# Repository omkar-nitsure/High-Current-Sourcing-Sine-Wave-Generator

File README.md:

# High Current Sourcing Sine Wave Generator

Group Members -

1. Omkar Nitsure - 210070057
2. Ojas Karanjkar - 210070040
3. Kushal Gajbe - 210070048
4. Vaibhav Garg - 21d070085 <br>
Github Link - [All files and code Contents](https://github.com/omkar-nitsure/High_Current_Sourcing_Sine_Wave_Generator)

## Introduction

Magnetic Materials are used in many application and in many different equipment for their special properties. But before using them, we need to have in-depth knowledge of their characteristics. This requires performing BH characterization. In BH characterization, we need to apply a sinusoidal voltage of varying amplitude and frequency across the magnetic material and check for the current it draws. Then the current and voltage information can be used to compute the value of B and H. The area enclosed by this curve is an indication of the amount of power dissipation in the material. This and other information is vital for choosing the right material for a specific application.

So, now we understand why BH characterization is important. We need a source which is able to generate a sinusoidal voltage with varying amplitude and frequency and source the current drawn by the magnetic material. The aim of our project is to design such a source.

This problem can be tackled either using a digital + analog or only analog approach. We tried both approaches. We designed an analog only circuit comprising of Class-AB amplifier and for the digital + analog we have used a Class-D amplifier based circuit. Let's discuss both the approaches in the following sections -

## Target Specifications

We were required to build a source satisfying the above constraints -

- Output Frequency = 2-3 kHz
- Output Sine amplitude = upto 30 Vpp
- Current Sourcing capacity = 1-1.5 A
- Added functionality of allowing user to change frequency on the go using a knob. - Display the current frequency on a LCD screen for ready reference

## Class Ab Based Circuit

In this approach, we designed a circuit which can be broken down in a Voltage amplification circuit and a Current sourcing circuit and connected them in cascade. The circuit diagram is as follows -

Figure 1: Circuit diagram for Class AB amplifier based circuit
The above circuit was giving the correct required output but there was an issue. There was a lot of power dissipation in the different BJTs which would have required big heat sinks and also a lot of power would have got wasted along with the unavoidable power loss due to eddy currents. We tried changing a lot of different parameters but we were not able to reduce the power-loss to the desired levels. While we were searching for the potential solution, we came across class-D amplifier which was not having the issue of power loss. After a lot of brainstorming, we decided to scrap this approach and continue with the approach involving Class-D amplifier.

## Class D Amplifier

Class D amplifier consists of a full-bridge MOSFET based circuit. Each of the 4 MOSFETs are fired by 4 different PWM signals across their gate-source. Two MOSFETs in the same leg get complementary PWM signal such that there ON times are separated by a non-zero dead time.

This dead-time is provided to ensure that there is sufficient time for the MOSFETs to change their states ensuring that both MOSFETs don't turn-on together and short Vdd with GND.

The duty ratio of the PWM signals vary sinusoidally which enables the output to be sinusoidal.

Duty ratios of the 4 PWM signals are as follows -

$$
d_{1} = \frac{1}{2} + m \sin(\omega t)
$$

$$
d_{2} = \frac{1}{2} - m \sin(\omega t)
$$

Then d3 and d4 are just complements of d1, d2 respectively seperated by dead time.

Figure 2: full-bridge MOSFET based circuit

## A. Simulations

We performed the LTSpice simulations of class D amplifier for our required specifications and got desired results. We generated the sinusoidally varying PWM signals by giving a triangular wave and a sine wave as inputs to a comparator. We kept zero dead time assuming perfect switching of MOSFETs. The MOSFETs were switching at a frequency of 100kHz and we tested the sinusoidal outputs for frequencies till 3kHz which was our target specification. We also checked for the power dissipation in the entire circuit(in all components) and found that they were in mW. Thus this approach allowed us to generate sine waves of large amplitudes for frequencies upto 3kHz without requiring any heat-sink at all!! This approach has some cons but that is a trade-off for excellent efficiency. The main limitation of this approach is that it generates saw-tooth noise because of MOSFET switching whereas a purely analog approach will not add any such noise. The results of our simulations are given below where the output voltage across the inductive load is given at the edge of our required specifications. We also give the corresponding current drawn by the inductive load which is well within our specifications.

Figure 3: output voltage across load

Figure 4: Current through the inductive load

## B. Choice Of Bom And Justifications

The Bill of Materials required for our circuit is as follows -

Figure 5: Bill of Materials

Gate Drivers - The PWM output cannot be directly given to the gates of MOSFETS as the back-currents generated while a MOSFET is turning-OFF will certainly damage the GPIO
pins on the Micro-controller. We wanted to have a gate driver which can amplify the rail-to-rail logic of 3.3 V coming from the micro-controller to rail-to-rail logic of 15V. We also wanted the current sinking capacity to be high which will allow us to switch at much higher frequency. Thus we chose the 2ED02012-FI gate driver from Infenion STM32 minimum package called Bluepill was more than sufficient for our ap-
Bluepill -
plication. It was able to generate the 4 independent PWM signals. It also had ADC which was used to provide the functionality of a knob for changing the output frequency to the user. We also needed 4 additional analog pins to write current frequency value on the LCD display. All of these requirements were satisfied by Bluepill.

RC filter at the input of the gate driver - This low-pass filter was used to remove the high-frequency peaks in the PWM outputs of the microcontroller.

MOSFET - We wanted to produce output sinusoidal signals of 30 Vyp and thus the Vas specifications of the MOSFETs must be larger than this value. We also wanted to source currents upto even 2A and thus the Ids rating must be larger than this value. We also wanted the MOSFET
to be a power MOSFET having the capability of very fast switching. MOSFET named IRF840 satidfied all these constraints and thus we chose that MOSFET for the circuit. LC circuit at the output - We had to use a low-pass filter at the output of a Class-D
amplifier to remove the saw-tooth noise added due to switching. We could have used a RC
filter but that would have resulted in large power-loss in the resistor, so we chose to use LC
filter of appropriate value which would not cause any power-loss.

## Microcontroller Programming

We generate the PWM signal with Sinusoidally varying dead time using the STM32 Bluepill microcontroller. The microcontroller clock frequency is 8MHz. The internal circuitry increases it such that the timers(which we used) get a frequency of 64MHz while the ADC sampling frequency is 8MHz. We decided to keep the switching frequency to be 100kHz which is almost 33 times larger than the maximum rated frequency of our system. It is also well within the maximum attainable switching frequency by the Power MOSFET. We have kept the cut-off frequency to be 12kHz which is less than 10 times the maximum rating. Let us now see how did we generate the PWM signal with sinusoidally varying duty ratio.

## A. Pwm Generation

We used 2 channels from TIM1 on the STM32. Each of these channels have a register named CCR which can be used to manipulate the duty ratio of the microcontroller. So, we stored the values for 1 cycle of the sinusoidal signals corresponding to d1 and d2 in the memory and read those values after a frequency dependent delay. This allowed us to generate sinusoidally varying PWM. Dead-time was also provided to ensure proper switching without any shorting which might damage the MOSFETs. We used a constant dead time of 0.125 us

## B. Adc Interfacing

We wanted to give a simple knob-based control to the user which he can use to set the output frequency he wants. This knob was made using a potentiometer circuit where the ends of the potentiometer are connected to the GND and 3.3V of the microcontroller. The middle pin is connected to the ADC and the values of voltage read using the ADC are then mapped to appropriate frequencies. The ADC is sampled every 1000 cycles to ensure that we don't sample "too often".

## C. Lcd Interfacing

We have also interfaced the LCD with the system so that user can see the current frequency output from the system in real time and adjust the knob accordingly to set the frequency of his choice. We implement the interfacing with 6 pins, 4 of which are the actual data pins. We write the frequency value after every 1000 cycles right after sampling the ADC. Thus we ensure that we don't write to the LCD "too often". The CAD model was then made accordingly to ensure that the LCD is clearly visible to the user.

Figure 6: LCD in the final prototype

## D. Microcontroller Pinout

The final microcontroller pinout after setting all the GPIO pins and interfacing the ADC and LCD is as follows -
s_JTCK-SW

Figure 7: STM32 pinout

## Schematics

Having selected the class D amplifier as the base of our power amplifier, we started making the overall complete circuitry for our prototype. As we have seen so far, our circuit majorly consists of 3 parts, viz

1. Microcontroller - For generating PWM signals.
2. Gate Drivers - For interfacing microcontroller with MOSFETs.
3. Full-bridge MOSFET
In our circuit, we have directly used Blue-Pill, which is a miniature version of NUCLEO-
F103RB STM32 evaluation board. The reason for going with blue-pill is simply because it contains all of the features of NUCLEO board we required and moreover, it is smaller in size.

However, one main issue while using blue-pill is that it does not have emulator part, which is present in NUCLEO board, making it difficult to dump code onto it. We had to use the ST-Link debugger everytime we wanted to dump our code onto blue-pill.

Moving onto the next part of our circuit, we have Gate Drivers. We chose the 2ED020I12-FI
IC manufactured by Infineon. The IC can sustain high voltage up to 1.2kV, supplying currents up to 1A or -2A. The PWM signals generated by the blue-pill were then fed to the gate drivers through the RC filter. This reduces the spike levels due to switching in the microcontroller.

A major part of the gate driver circuitry is the Bootstrap circuit at the high-side output of the gate driver IC. The bootstrap circuitry is used to supply bias to high-side FET. When the low-side FET is ON, the HS pin and source of the high-side FET are pulled to the ground.

As a result, the bootstrap capacitor is charged to Vdd. When the high-side FET is ON in the next cycle, the bootstrap capacitor discharges some of its charge to the gate of FET, thereby creating some positive Vgs and turning on the FET. Schottky diode is used as the bootstrap diode because of its ability to switch at high frequencies. Calculation of bootstrap capacitance is an important step while designing the bootstrap circuit. The value of bootstrap capacitor is calculated according to the given formula -

Figure 8: Gate Driver Circuit
For IRF540N, the value of gate charge is 66nC, and for 1N5822 Schottky diode, the forward voltage drop is 0.525 V, and Vdd = 15V. Plugging the values in above formula gives, Cg =
4.56 nF The minimum value of bootstrap capacitance should be chosen such that, Cboot =
10xCg Therefore, the value of bootstrap capacitor should be atleast 45nF. Apart from that, we also need to add a bypass capacitor value to Vdd, and the value of bypass capacitor should be atleast 10x the bootstrap capacitance. Therefore, Cbypass should be atleast 450nF.

Now, finally, once we have the pulses at the output of gate drivers, they are passed onto the respective gates of the FETs. The pulses are passed onto the gates of FETs through a resistor.

The output is observed between the source of the two high-side FETs. An electrolytic capacitor is connected between the Vdd and GND and ceramic capacitors need to be connected betweent the drain and ground of each FET. A simple low pass filtering is performed at the output to

Figure 9: Class-D amplifier
remove spikes due to switching.

We have also added a provision in our circuit to control the frequency using a knob. The knob is connected to a 10kΩ potentiometer. Based on the voltage at the middle terminal of the the voltage is sensed by the ADC in the blue-pill and it is mapped to the corresponding frequency value. The current frequency value is displayed using an LCD. Finally, putting all parts together, we get our final circuit schematics.

Figure 10: Full circuit schematics

## Intermediate Testing

## A. Pwm Generation

As descibed in 5.1, we generated the PWM signals using STM32 and tested. The output is shown in the image below.

Figure 11: PWM testing

## B. Adc Interfacing

We were able to interface a potentiometer with the microcontroller using an ADC successfully.

## C. Breadboard Testing

## Pcb Design

We designed the PCB using the KiCAD software. Various layout rules such as obtuse angles between tracks, decoupling capacitors, and correct placement of components were taken care of. We have used both SMD and THT components in our design. We have majorly used SM
components for decoupling capacitors and the gate driver IC. We have used screw terminals for connecting the inputs to the PCB. The blue pill is mounted on the PCB using a breakout board.

Figure 12: PCB Layout

Figure 13: PCB with all components

Figure 14: PCB for breakout board

Figure 15: Final PCB

## Cad Design

For our CAD design, we initially planned a 3D box structure using Fusion 360 software. The design process involved careful planning to ensure accessibility to certain components from the outside world while the prototype remains inside the box.

## A. Design Requirements

1. LCD Display: The design incorporates an open area for the LCD display to allow users to observe the frequency without obstruction.

2. Input and Outputs:

- Power Supply: A 5V supply is provided through a USB cable, which is also utilized for burning code onto the STM32 microcontroller.
- External Supplies: Vdrive and Vdd are supplied externally.
- Output Access: The output across the capacitor is also accessible through an opening on the 3D box.
- Potentiometer: A potentiometer is mounted on the box which will be used for controlling the frequency of the prototype. Thus, certain areas must be opened up on the box for the same.

Figure 16: 3D box CAD design
However, after discussing the design with the faculty we concluded that 3D printing the box is not possible, and hence we would have to use acrylic sheets laser cutting to make our box.

Now, makercase was used for making the dxf file which has the thickness of the sheet, length, and width for each side of the box. After importing this dxf file into the Fusion 360 software, we cut out the same regions as in the 3D box design.

Figure 17: Acrylic sheets design for the box

|  |  |
| ----------------------------------- | ----------------------------------- |
| (a) Top side                        | (b) Bottom side                     |

|  |  |
| ----------------------------------- | ----------------------------------- |
| (c) Front view side                 | (d) Side view                       |

Figure 18: Dimensions and open areas in the design.

## Final Prototype

Figure 19: Final Prototype

## Results

Figure 20: Final output Sine waveform
Our final output waveform is a sine wave meticulously designed for the characterization of magnetic materials. The waveform is derived from three power sources: Vdrive, Vdd, and a 5V supply via USB to the Nucleo board. The output signal is measured across a 470nF capacitor. Our setup achieves a current rating of 1.4 A, with the peak-to-peak voltage (Vpp) reaching up to 30 V at a frequency of 500Hz.

Figure 21: Gate Driver output

The output from the gate driver pertains to the high side. As anticipated, it effectively amplifies the PWM signal from the microcontroller. We are able to achieve 18.6 V of peak-topeak voltage output from the gate driver.

Figure 22: Microcontroller output. 
Above is the microcontroller PWM output. This goes as an input to our gate drivers. This PWM peak-to-peak voltage is 3.84 V. This is then amplified to 18.6 V by the gate drivers.

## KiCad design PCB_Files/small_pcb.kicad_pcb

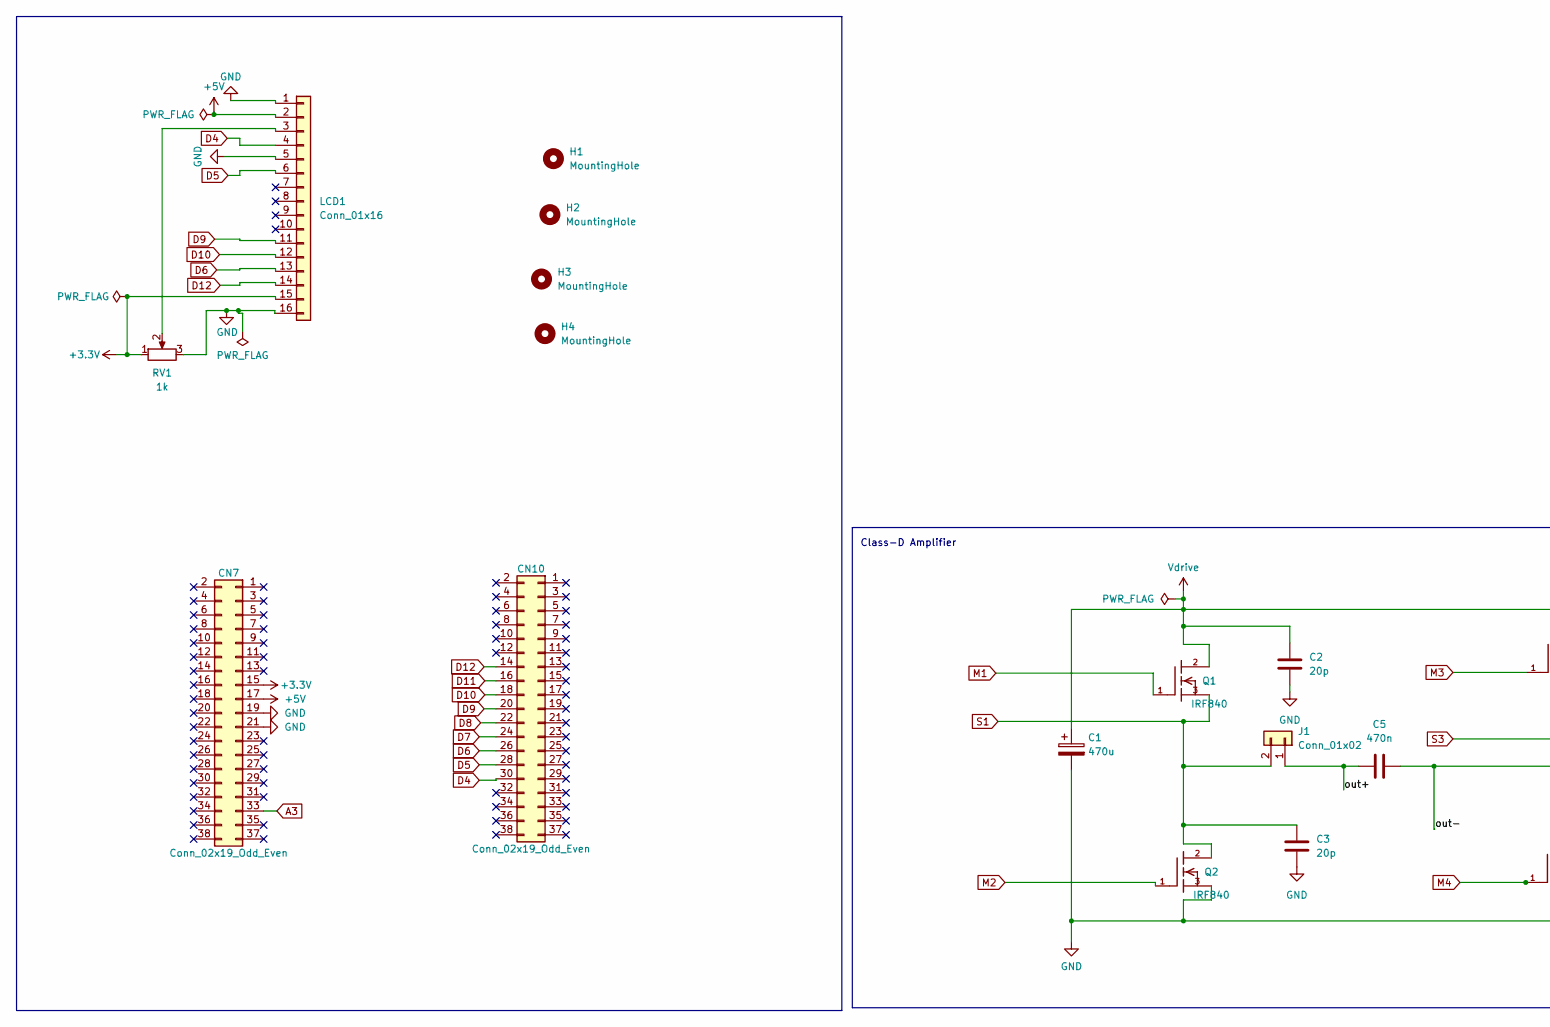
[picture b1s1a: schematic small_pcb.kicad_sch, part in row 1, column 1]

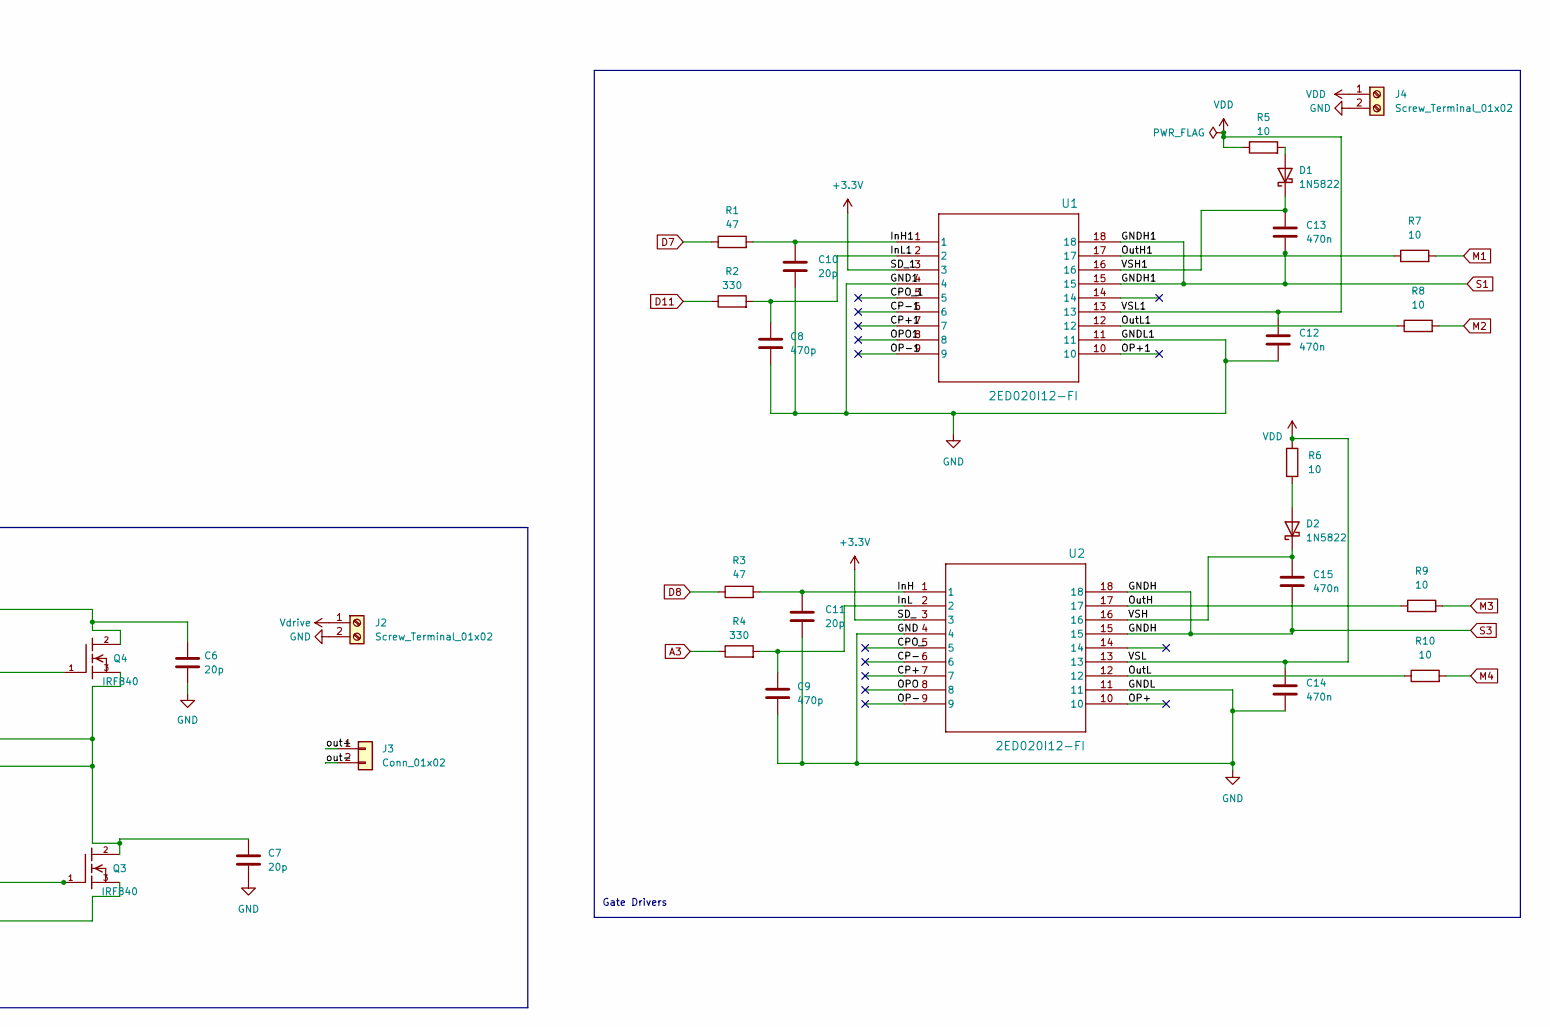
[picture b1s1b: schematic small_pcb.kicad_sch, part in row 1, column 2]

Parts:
C1: 470u; CP_Radial_D10.0mm_P5.00mm
C2, C3, C6, C7, C10, C11: 20p; C_0805_2012Metric_Pad1.18x1.45mm_HandSolder
C5, C12, C13, C14, C15: 470n; C_1206_3216Metric_Pad1.33x1.80mm_HandSolder
C8, C9: 470p; C_0805_2012Metric_Pad1.18x1.45mm_HandSolder
CN7, CN10: Conn_02x19_Odd_Even; PinSocket_2x19_P2.54mm_Vertical
D1, D2: 1N5822; D_DO-201AD_P15.24mm_Horizontal
H1, H2, H3, H4: MountingHole; MountingHole_3mm
J1, J3: Conn_01x02; PinSocket_1x02_P2.54mm_Vertical
J2, J4: Screw_Terminal_01x02; TerminalBlock_Altech_AK300-2_P5.00mm
LCD1: Conn_01x16; PinSocket_1x16_P2.54mm_Vertical
Q1, Q2, Q3, Q4: IRF840; TO-220-1
R1, R3: 47; R_0805_2012Metric_Pad1.20x1.40mm_HandSolder
R2, R4: 330; R_0805_2012Metric_Pad1.20x1.40mm_HandSolder
R5, R6, R7, R8, R9, R10: 10; R_Axial_DIN0309_L9.0mm_D3.2mm_P12.70mm_Horizontal
RV1: 1k; Potentiometer_Bourns_3386X_Horizontal
U1, U2: 2ED020I12-FI; PG-DSO-18-2_INF

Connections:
+3.3V: CN7.15, LCD1.15, RV1.1, U1.3, U2.3
+5V: CN7.17, LCD1.2
/CP+: U2.7
/CP+1: U1.7
/CP-: U2.6
/CP-1: U1.6
/CPO_: U2.5
/CPO_1: U1.5
/InH: C11.1, R3.2, U2.1
/InH1: C10.1, R1.2, U1.1
/InL: C9.1, R4.2, U2.2
/InL1: C8.1, R2.2, U1.2
/OP+: U2.10
/OP+1: U1.10
/OP-: U2.9
/OP-1: U1.9
/OPO: U2.8
/OPO1: U1.8
/OutH: R9.1, U2.17
/OutH1: R7.1, U1.17
/OutL: R10.1, U2.12
/OutL1: R8.1, U1.12
/VSH: C15.1, D2.1 (K), U2.16
/VSH1: C13.1, D1.1 (K), U1.16
/out+: C5.1, J1.1, J3.1
A3: CN7.33, R4.1
D4: CN10.30, LCD1.4
D5: CN10.28, LCD1.6
D6: CN10.26, LCD1.13
D7: CN10.24, R1.1
D8: CN10.22, R3.1
D9: CN10.20, LCD1.11
D10: CN10.18, LCD1.12
D11: CN10.16, R2.1
D12: CN10.14, LCD1.14
GND: C1.2, C2.2, C3.2, C6.2, C7.2, C8.2, C9.2, C10.2, C11.2, C12.2, C14.2, CN7.19, CN7.21, J2.2, J4.2, LCD1.1, LCD1.5, LCD1.16, Q2.3, Q3.3, RV1.3, U1.4, U1.11, U2.4, U2.11
M1: Q1.1, R7.2
M2: Q2.1, R8.2
M3: Q4.1, R9.2
M4: Q3.1, R10.2
unnamed: D1.2 (A), R5.2
unnamed: D2.2 (A), R6.2
unnamed: LCD1.3, RV1.2
S1: C3.1, C13.2, J1.2, Q1.3, Q2.2, U1.15, U1.18
S3: C5.2, C7.1, C15.2, J3.2, Q3.2, Q4.3, U2.15, U2.18
VDD: C12.1, C14.1, J4.1, R5.1, R6.1, U1.13, U2.13
Vdrive: C1.1, C2.1, C6.1, J2.1, Q1.2, Q4.2

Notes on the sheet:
Class-D Amplifier
Gate Drivers

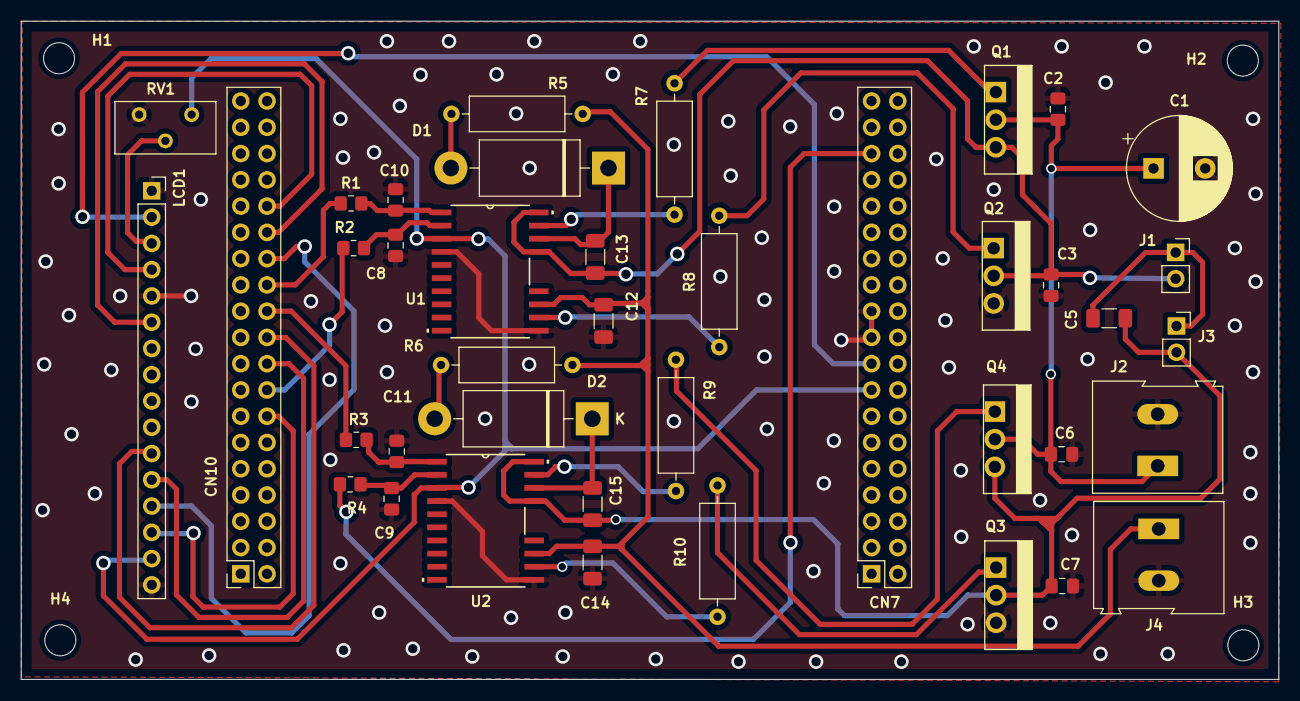
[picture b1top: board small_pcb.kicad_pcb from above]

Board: 2 copper layers, 121.6 x 63.7 mm, 44 parts (0 on the bottom side), 35 nets.

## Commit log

2024-05-25 all resources for EDL project
2024-09-20 added README
